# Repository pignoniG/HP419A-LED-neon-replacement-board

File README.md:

# HP419A-LED-neon-replacement-board
HP419A LED neon Replacement board (based on Mr.Carson's lab design)
This board replaces the neons in a HP419A, as well as the oscillator circuit, should be powered by the + - 13v (battery + battery - lines )

You will have to adjust led current based on your LED, with mine os5rpm57e1a (https://www.tme.eu/it/details/os5rpm57e1a-mn/diodi-led-tht-rotondi/optosupply/) i settled on powering them with 2.5K ohm in series.

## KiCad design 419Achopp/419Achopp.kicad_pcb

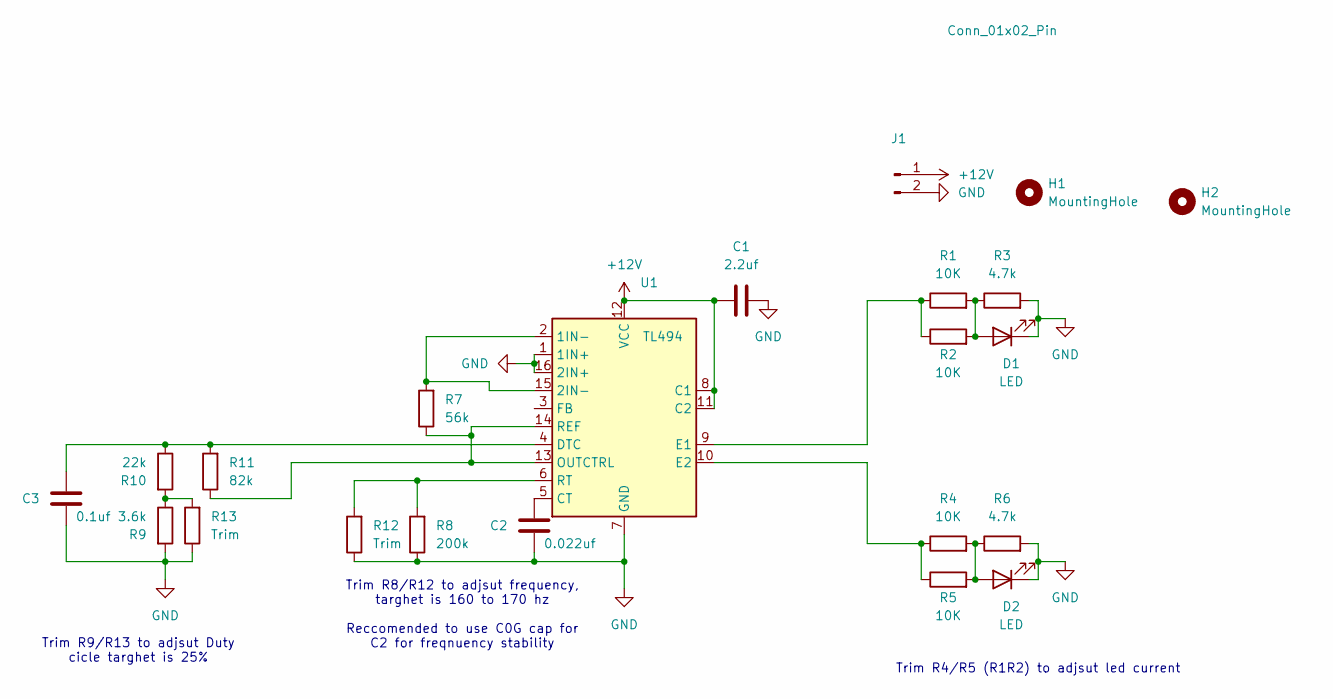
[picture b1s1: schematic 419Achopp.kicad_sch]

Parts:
C1: 2.2uf; R_1206_3216Metric
C2: 0.022uf; R_1206_3216Metric
C3: 0.1uf; R_1206_3216Metric
D1, D2: LED; LED_D5.0mm_Clear
H1, H2: MountingHole; MountingHole_3.7mm
J1: Conn_01x02_Pin; PinHeader_2x01_P2.00mm_Vertical
R1, R2, R4, R5: 10K; R_1206_3216Metric
R3, R6: 4.7k; R_1206_3216Metric
R7: 56k; C_0805_2012Metric
R8: 200k; C_0805_2012Metric
R9: 3.6k; C_0805_2012Metric
R10: 22k; C_0805_2012Metric
R11: 82k; C_0805_2012Metric
R12, R13: Trim; C_0805_2012Metric
U1: TL494; SOIC-16_3.9x9.9mm_P1.27mm

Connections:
+12V: C1.1, J1.1, U1.8 (C1), U1.11 (C2), U1.12 (VCC)
GND: C1.2, C2.1, C3.1, D1.1 (K), D2.1 (K), J1.2, R3.2, R6.2, R8.1, R9.2, R12.1, R13.1, U1.1 (1IN+), U1.7 (GND), U1.16 (2IN+)
unnamed: D1.2 (A), R1.2, R2.2, R3.1
unnamed: D2.2 (A), R4.2, R5.2, R6.1
unnamed: R9.1, R10.2, R13.2
unnamed: R7.2, U1.2 (1IN-), U1.15 (2IN-)
unnamed: C2.2, U1.5 (CT)
unnamed: C3.2, R10.1, R11.2, U1.4 (DTC)
unnamed: R1.1, R2.1, U1.9 (E1)
unnamed: R4.1, R5.1, U1.10 (E2)
unnamed: R7.1, R11.1, U1.13 (OUTCTRL), U1.14 (REF)
unnamed: R8.2, R12.2, U1.6 (RT)

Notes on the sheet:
Trim R8/R12 to adjsut frequency, targhet is 160 to 170 hz Reccomended to use C0G cap for C2 for freqnuency stability
Trim R4/R5 (R1R2) to adjsut led current
Trim R9/R13 to adjsut Duty cicle targhet is 25%

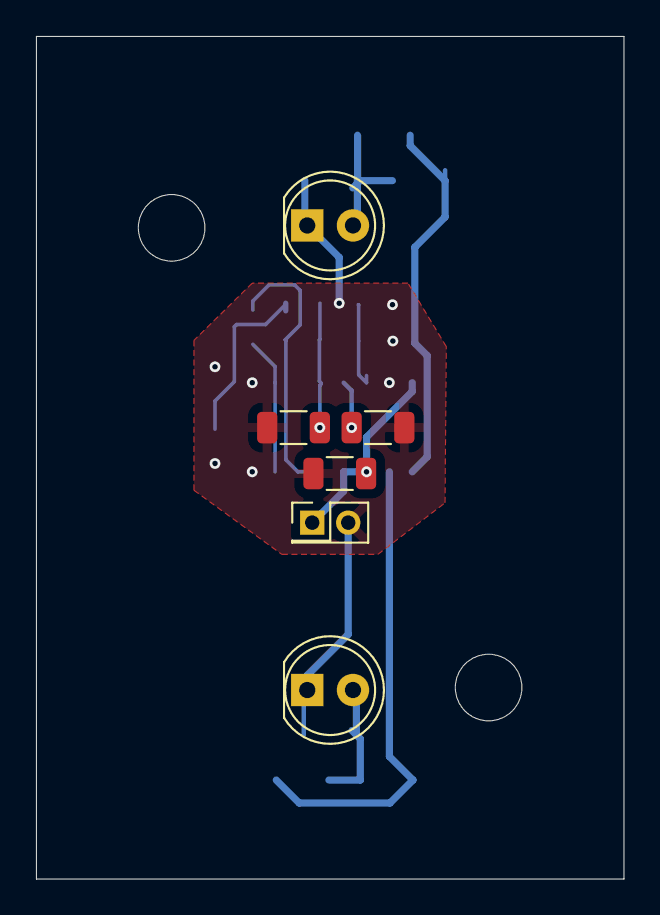
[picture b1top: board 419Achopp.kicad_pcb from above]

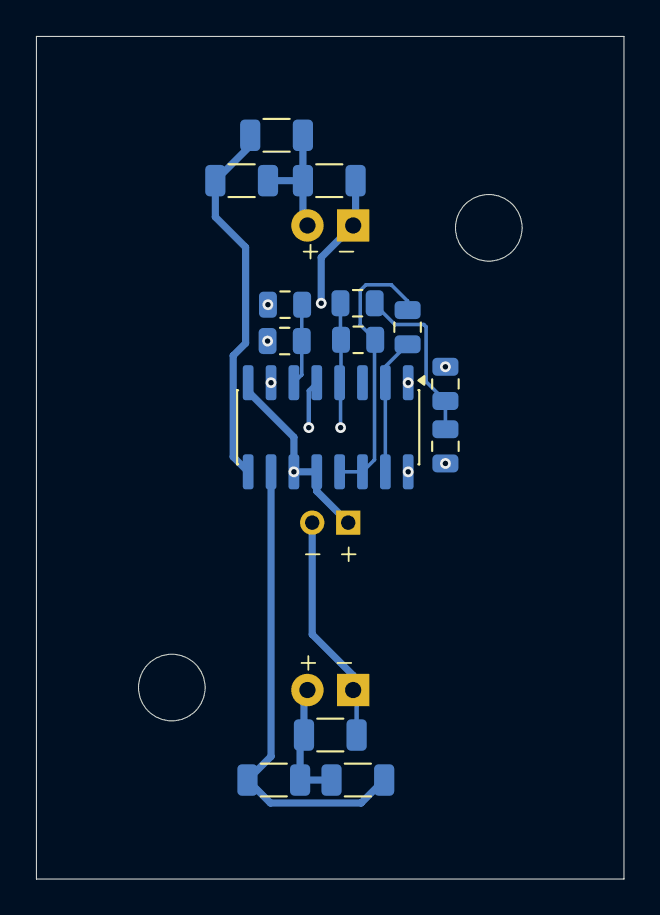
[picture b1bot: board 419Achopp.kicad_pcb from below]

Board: 2 copper layers, 32.6 x 46.8 mm, 22 parts (14 on the bottom side), 12 nets.

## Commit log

2026-05-28 Add files via upload
    init
2026-05-28 Update README with LED current and power info
    Added details about LED current adjustment and power requirements.
